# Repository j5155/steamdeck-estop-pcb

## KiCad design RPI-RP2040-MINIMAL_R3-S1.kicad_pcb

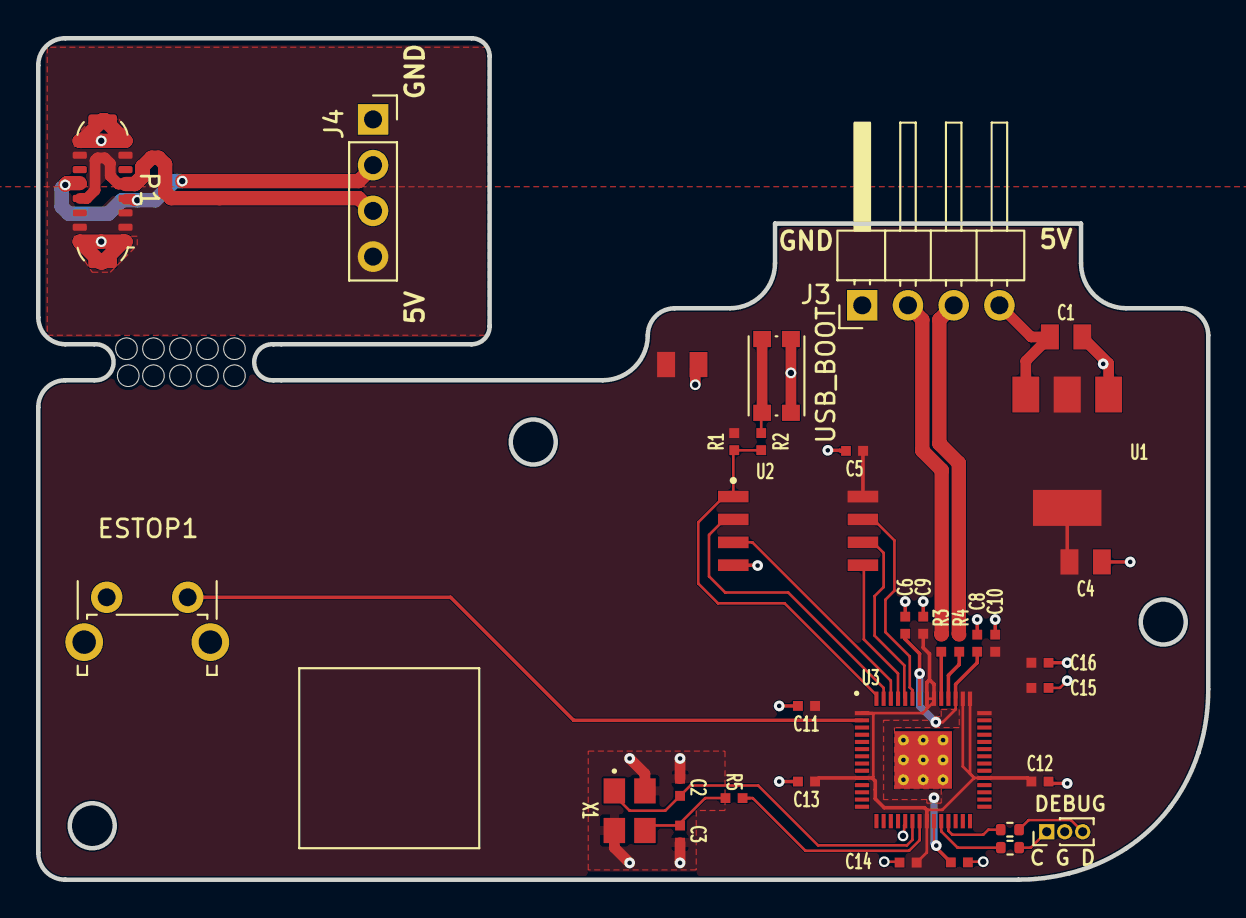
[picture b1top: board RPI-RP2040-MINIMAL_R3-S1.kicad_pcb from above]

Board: 2 copper layers, 65.0 x 46.7 mm, 34 parts (0 on the bottom side), 27 nets.

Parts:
BOOT_SEL1: SW_Push; SW_Push_1P1T_NO_CK_KMR2
C1, C4, C17: 10u; generic_capc2012x125
C2, C3: 15p; generic_capc1005x50
C5, C6, C7, C9, C11, C12, C13, C14, C15, C16: 100n; generic_capc1005x50
C8, C10: 1u; generic_capc1005x50
ESTOP1: SW_Push; SW_Tactile_SPST_Angled_PTS645Vx31-2LFS
J1: Conn_01x03_Socket; PinHeader_1x03_P1.00mm_Vertical
J3: Conn_01x04_Pin; PinHeader_1x04_P2.54mm_Horizontal
J4: Conn_01x04_Socket; PinSocket_1x04_P2.54mm_Vertical
P1: USB_C_Plug_USB2.0; USB_C_Plug_ShenzhenJingTuoJin_918-118A2021Y40002_Vertical
R1, R5: 1k; generic_resc1005x35
R2: 10k; generic_resc1005x35
R3, R4: 27; generic_resc1005x35
R6, R7: 100; R_0402_1005Metric
U1: NCP1117ST33T3G; onsemi_ncp1117st33t3g
U2: W25Q128JVSIQ; generic_soic127p790x195-8
U3: RP2040; rpi_rp2040_vias
X1: 12MHz; generic_xtalcc320x250x80-4

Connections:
+1V1: C6.1, C7.1, C8.1, U3.23 (DVDD), U3.45 (VREG_VOUT), U3.50 (DVDD)
+3V3: C4.1, C5.1, C9.1, C10.1, C11.1, C12.1, C13.1, C14.1, C15.1, C16.1, C17.1, R2.1, U1.2 (OUT), U1.4 (OUT), U2.8 (VCC), U3.1 (IOVDD), U3.10 (IOVDD), U3.22 (IOVDD), U3.33 (IOVDD), U3.42 (IOVDD), U3.43 (ADC_AVDD), U3.44 (VREG_IN), U3.48 (USB_VDD), U3.49 (IOVDD)
/BRIDGE_GND: J4.1, P1.A1 (GND), P1.A12 (GND), P1.B1 (GND), P1.B12 (GND), P1.SH (SHIELD)
/BRIDGE_USBD+: J4.2, P1.A6 (D+), P1.B6
/BRIDGE_USBD-: J4.3, P1.A7 (D-), P1.B7
/BRIDGE_VBUS: J4.4, P1.A4 (VBUS), P1.A5 (CC), P1.A9 (VBUS), P1.B4 (VBUS), P1.B9 (VBUS)
/GPIO0: ESTOP1.2, U3.2 (GPIO0)
/QSPI_SCLK: U2.6 (CLK), U3.52 (QSPI_SCLK)
/QSPI_SD0: U2.5 (DI_IO0), U3.53 (QSPI_SD0)
/QSPI_SD1: U2.2 (DO_IO1), U3.55 (QSPI_SD1)
/QSPI_SD2: U2.3 (~WP_IO2), U3.54 (QSPI_SD2)
/QSPI_SD3: U2.7 (~HOLD_IO3), U3.51 (QSPI_SD3)
/QSPI_SS: R1.1, R2.2, U2.1 (~CS), U3.56 (QSPI_~SS)
/SWCLK: R6.1, U3.24 (SWCLK)
/SWD: R7.1, U3.25 (SWD)
/USB_D+: J3.2, R3.1
/USB_D-: J3.3, R4.1
/XIN: C2.1, U3.20 (XIN), X1.1
/XOUT: R5.2, U3.21 (XOUT)
/~USB_BOOT: BOOT_SEL1.2, R1.2
GND: BOOT_SEL1.1, C1.2, C2.2, C3.2, C4.2, C5.2, C6.2, C7.2, C8.2, C9.2, C10.2, C11.2, C12.2, C13.2, C14.2, C15.2, C16.2, C17.2, ESTOP1.1, J1.2, J3.1, U1.1 (GND), U2.4 (GND), U3.19 (TESTEN), U3.57 (GND), X1.2, X1.4
unnamed: C3.1, R5.1, X1.3
unnamed: J1.1, R6.2
unnamed: J1.3, R7.2
unnamed: R4.2, U3.46 (USB_DM)
unnamed: R3.2, U3.47 (USB_DP)
VBUS: C1.1, J3.4, U1.3 (IN)

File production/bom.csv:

Designator,Footprint,Quantity,Value,LCSC Part #
BOOT_SEL1,SW_Push_1P1T_NO_CK_KMR2,1,SW_Push,
"C1, C17, C4",generic_capc2012x125,3,10u,
"C10, C8",generic_capc1005x50,2,1u,
"C11, C12, C13, C14, C15, C16, C5, C6, C7, C9",generic_capc1005x50,10,100n,
"C2, C3",generic_capc1005x50,2,15p,
ESTOP1,SW_Tactile_SPST_Angled_PTS645Vx31-2LFS,1,SW_Push,
J1,PinHeader_1x03_P1.00mm_Vertical,1,Conn_01x03_Socket,
J3,PinHeader_1x04_P2.54mm_Horizontal,1,Conn_01x04_Pin,
J4,PinSocket_1x04_P2.54mm_Vertical,1,Conn_01x04_Socket,
P1,USB_C_Plug_ShenzhenJingTuoJin_918-118A2021Y40002_Vertical,1,USB_C_Plug_USB2.0,
"R1, R5",generic_resc1005x35,2,1k,
R2,generic_resc1005x35,1,10k,
"R3, R4",generic_resc1005x35,2,27,
"R6, R7",0402,2,100,C25076
U1,onsemi_ncp1117st33t3g,1,NCP1117ST33T3G,
U2,generic_soic127p790x195-8,1,W25Q128JVSIQ,
U3,rpi_rp2040_vias,1,RP2040,
X1,generic_xtalcc320x250x80-4,1,12MHz,
